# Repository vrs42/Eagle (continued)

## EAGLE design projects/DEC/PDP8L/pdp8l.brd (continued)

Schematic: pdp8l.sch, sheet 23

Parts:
A14: M115; H807
A15, A16: M162; H807
B15: M119; H807
B16, B17: M162; H807
C16: M111; H807

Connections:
!CLR_PARITY_ERROR: A14.M1 (IN3), B15.J2 (OUT)
!MB00: B16.A1 (1B); also elsewhere on the board
!MB01: B16.B1 (2B); also elsewhere on the board
!MB02: B16.C1 (4B); also elsewhere on the board
!MB03: B15.H2 (IN8), B15.N2 (IN8), B16.D1 (8B); also elsewhere on the board
!MB04: B15.F2 (IN7), B15.M2 (IN7), B17.K2 (1B); also elsewhere on the board
!MB05: B17.L2 (2B); also elsewhere on the board
!MB06: B15.D2 (IN5), B15.K2 (IN5), B17.M2 (4B); also elsewhere on the board
!MB07: B15.D1 (IN4), B15.K1 (IN4), B17.N2 (8B); also elsewhere on the board
!MB08: B15.C1 (IN3), B15.J1 (IN3), B16.K2 (1B); also elsewhere on the board
!MB09: B16.L2 (2B); also elsewhere on the board
!MB10: B16.M2 (4B); also elsewhere on the board
!MB11: B16.N2 (8B); also elsewhere on the board
!MEM00: A15.A1 (1B), C16.D2 (OUT)
!MEM01: A15.B1 (2B), C16.E1 (OUT)
!MEM02: A15.C1 (4B), C16.F2 (OUT)
!MEM03: A15.D1 (8B), C16.H1 (OUT)
!MEM04: A16.K2 (1B), C16.J2 (OUT)
!MEM05: A16.L2 (2B), C16.K1 (OUT)
!MEM06: A16.M2 (4B), C16.L2 (OUT)
!MEM07: A16.N2 (8B), C16.M1 (OUT)
!MEM08: A15.K2 (1B), C16.N2 (OUT)
!MEM09: A15.L2 (2B), C16.P1 (OUT)
!MEM10: A15.M2 (4B), C16.R2 (OUT)
!MEM11: A15.N2 (8B), C16.S1 (OUT)
!MEM_P: A16.D1 (8B), C16.B1 (OUT)
!MP_INT: B15.F1 (IN1), C16.T2 (OUT); also elsewhere on the board
!MP_SKIP: B15.P2 (OUT); also elsewhere on the board
A14M2: A14.K1 (IN1), A14.L1 (IN2), A14.M2 (OUT)
A14U1: A14.J2 (IN1), A14.U1 (OUT)
A15K1: A15.K1 (ODD), A16.E1 (1A)
A15L1: A15.L1 (EVEN), A16.A1 (1B)
A15U2: A15.U2 (ODD), A16.H1 (4A)
A15V2: A15.V2 (EVEN), A16.C1 (4B)
A16U2: A16.F1 (2A), A16.U2 (ODD)
A16V2: A16.B1 (2B), A16.V2 (EVEN)
B15U1: B15.U1, B17.D1 (8B)
B16K1: B16.K1 (ODD), B17.E1 (1A)
B16L1: B16.L1 (EVEN), B17.A1 (1B)
B16U2: B16.U2 (ODD), B17.H1 (4A)
B16V2: B16.V2 (EVEN), B17.C1 (4B)
B17U2: B17.F1 (2A), B17.U2 (ODD)
B17V2: B17.B1 (2B), B17.V2 (EVEN)
GND: A14.C2 (GND), A14.T1 (GND), A15.C2 (GND), A15.T1 (GND), A16.C2 (GND), A16.T1 (GND), B15.C2 (GND), B15.T1 (GND), B16.C2 (GND), B16.T1 (GND), B17.C2 (GND), B17.J1 (8A), B17.T1 (GND), C16.C2 (GND), C16.T1 (GND); also elsewhere on the board
IOP1: B15.H1 (IN2); also elsewhere on the board
IOP4: B15.A1 (IN1), B15.B1 (IN2); also elsewhere on the board
MB00: B16.E1 (1A); also elsewhere on the board
MB01: B16.F1 (2A); also elsewhere on the board
MB02: B16.H1 (4A); also elsewhere on the board
MB03: B16.J1 (8A); also elsewhere on the board
MB04: B17.P2 (1A); also elsewhere on the board
MB05: B15.E2 (IN6), B15.L2 (IN6), B17.R2 (2A); also elsewhere on the board
MB06: B17.S2 (4A); also elsewhere on the board
MB07: B17.T2 (8A); also elsewhere on the board
MB08: B16.P2 (1A); also elsewhere on the board
MB09: B16.R2 (2A); also elsewhere on the board
MB10: B16.S2 (4A); also elsewhere on the board
MB11: B16.T2 (8A); also elsewhere on the board
MB_PARITY_ODD: B17.K1 (ODD); also elsewhere on the board
MEM00: A15.E1 (1A), C16.C1 (IN); also elsewhere on the board
MEM01: A15.F1 (2A), C16.D1 (IN); also elsewhere on the board
MEM02: A15.H1 (4A), C16.E2 (IN); also elsewhere on the board
MEM03: A15.J1 (8A), C16.F1 (IN); also elsewhere on the board
MEM04: A16.P2 (1A), C16.H2 (IN); also elsewhere on the board
MEM05: A16.R2 (2A), C16.J1 (IN); also elsewhere on the board
MEM06: A16.S2 (4A), C16.K2 (IN); also elsewhere on the board
MEM07: A16.T2 (8A), C16.L1 (IN); also elsewhere on the board
MEM08: A15.P2 (1A), C16.M2 (IN); also elsewhere on the board
MEM09: A15.R2 (2A), C16.N1 (IN); also elsewhere on the board
MEM10: A15.S2 (4A), C16.P2 (IN); also elsewhere on the board
MEM11: A15.T2 (8A), C16.R1 (IN); also elsewhere on the board
MEM_P: A16.J1 (8A), C16.A1 (IN); also elsewhere on the board
MEM_PARITY_EVEN: A14.P1 (IN1), A14.R1 (IN2), A16.L1 (EVEN)
MP_INT: A14.K2 (IN2), A14.L2 (IN3), A14.N1 (OUT), C16.S2 (IN)
TP3: A14.S1 (IN3); also elsewhere on the board
VCC: A14.A2 (VCC), A15.A2 (VCC), A16.A2 (VCC), B15.A2 (VCC), B16.A2 (VCC), B17.A2 (VCC), C16.A2 (VCC); also elsewhere on the board

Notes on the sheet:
Borrowed Gates from A14 may not match DEC implementation.
Memory Parity

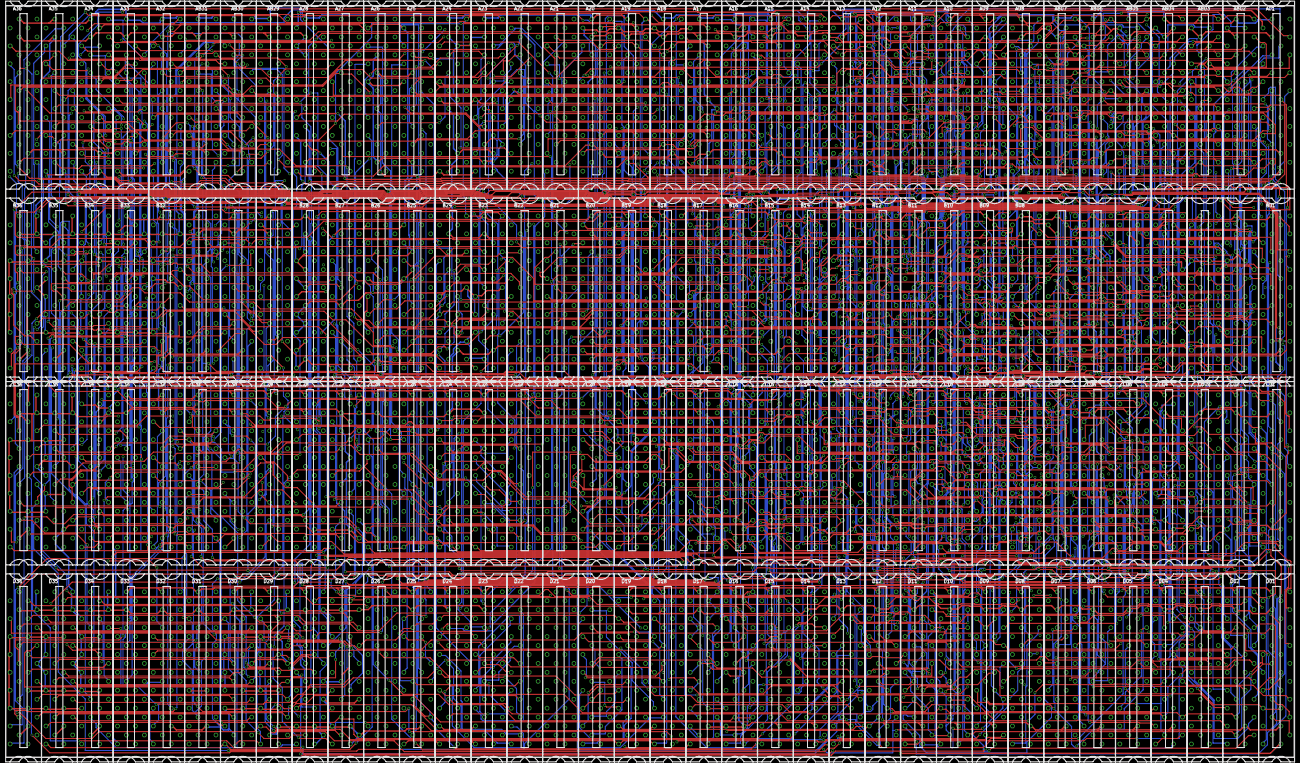
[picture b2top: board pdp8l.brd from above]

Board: 4 copper layers, 457.2 x 266.7 mm, 152 parts (0 on the bottom side), 895 nets.

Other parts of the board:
U$1, U$2, U$3, U$4, U$5, U$6, U$7, U$8, U$9, U$10, U$11, U$12, U$13, U$14, U$15, U$16, U$17, U$18: CBLOCK

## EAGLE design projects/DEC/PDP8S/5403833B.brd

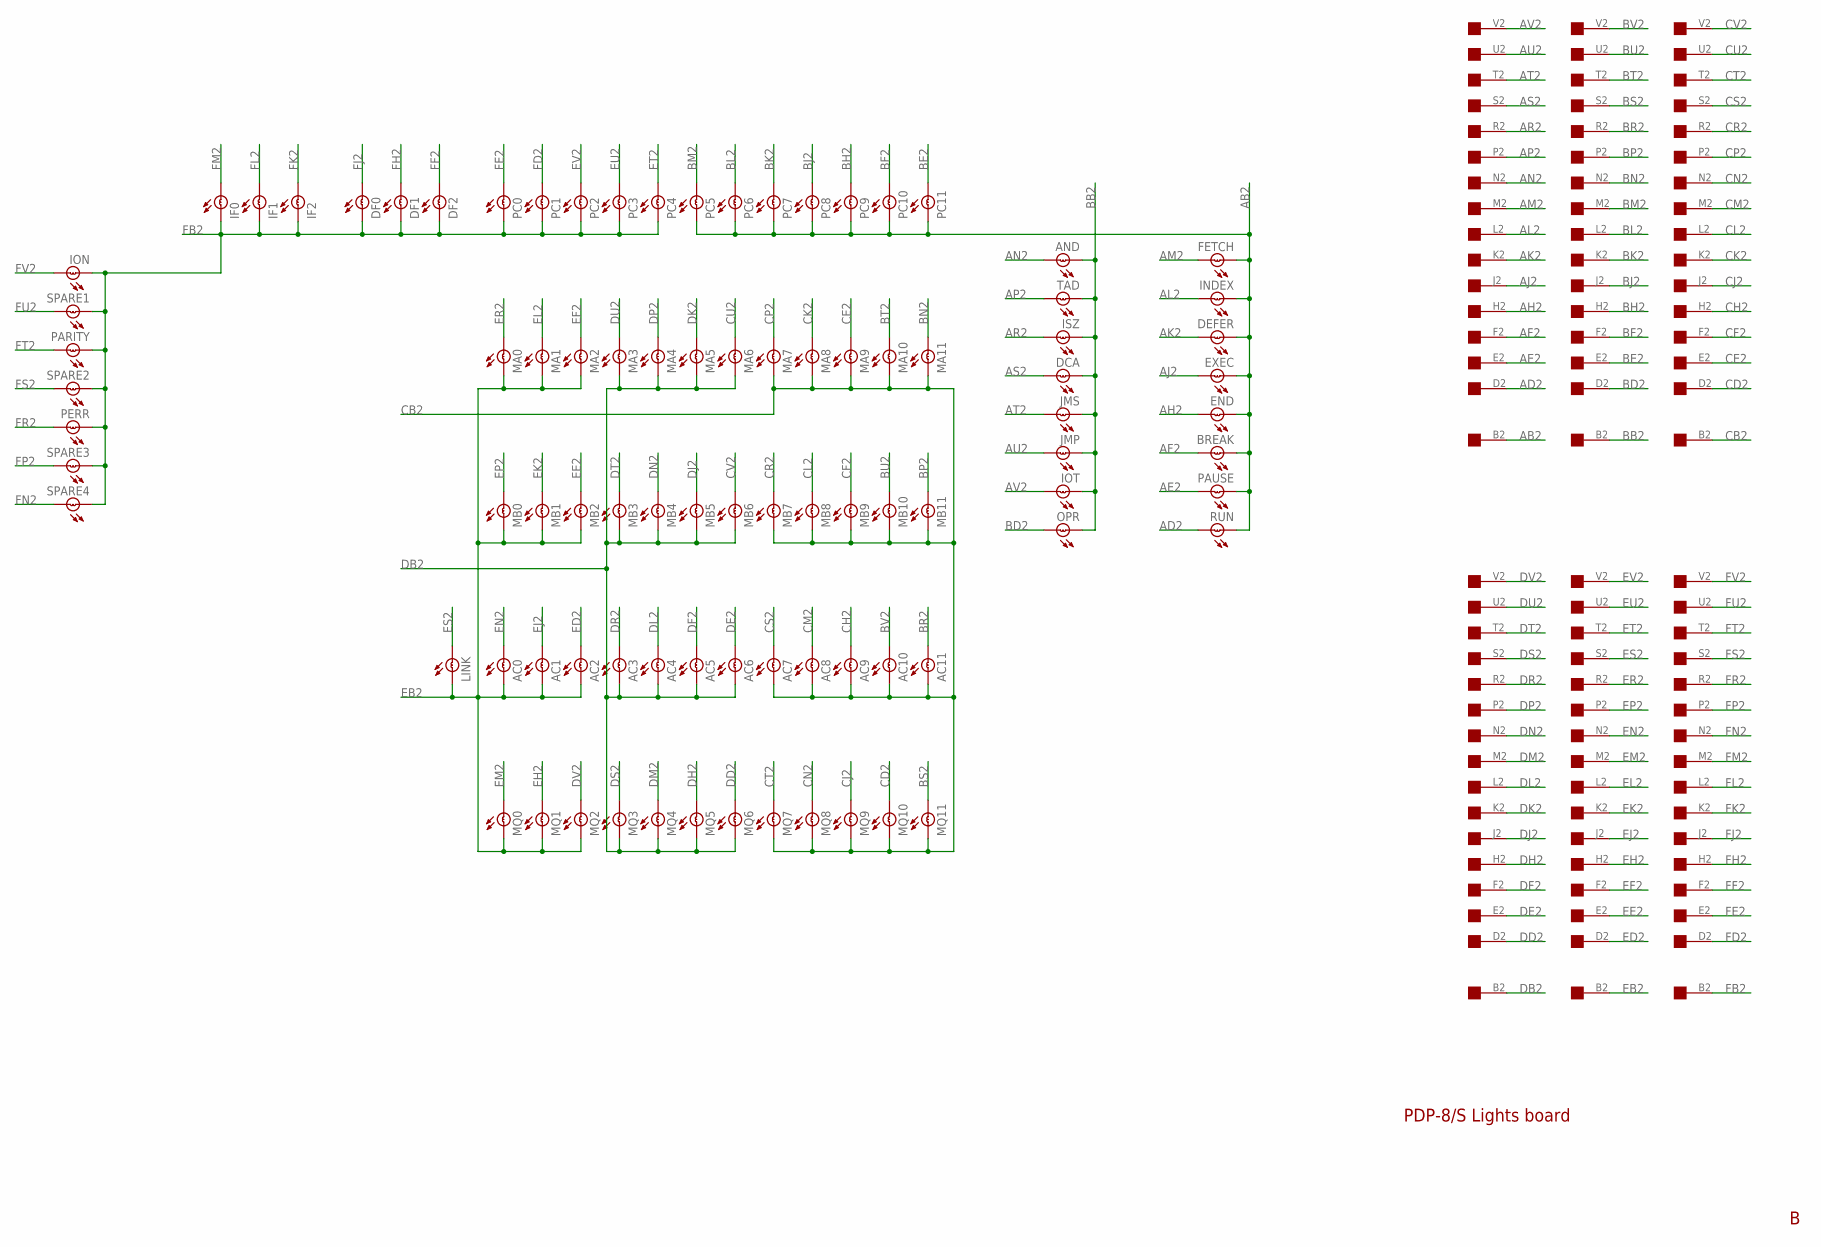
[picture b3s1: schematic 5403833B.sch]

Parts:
A: EDGE-1; EDGE-CON1
AC0, AC1, AC2, AC3, AC4, AC5, AC6, AC7, AC8, AC9, AC10, AC11: BULB
AND: BULB
B: EDGE-1; EDGE-CON1
BREAK: BULB
C: EDGE-1; EDGE-CON1
D: EDGE-1; EDGE-CON1
DCA: BULB
DEFER: BULB
DF0, DF1, DF2: BULB
E: EDGE-1; EDGE-CON1
END: BULB
EXEC: BULB
F: EDGE-1; EDGE-CON1
FETCH: BULB
IF0, IF1, IF2: BULB
INDEX: BULB
ION: BULB
IOT: BULB
ISZ: BULB
JMP: BULB
JMS: BULB
LINK: BULB
MA0, MA1, MA2, MA3, MA4, MA5, MA6, MA7, MA8, MA9, MA10, MA11: BULB
MB0, MB1, MB2, MB3, MB4, MB5, MB6, MB7, MB8, MB9, MB10, MB11: BULB
MQ0, MQ1, MQ2, MQ3, MQ4, MQ5, MQ6, MQ7, MQ8, MQ9, MQ10, MQ11: BULB
OPR: BULB
PARITY: BULB
PAUSE: BULB
PC0, PC1, PC2, PC3, PC4, PC5, PC6, PC7, PC8, PC9, PC10, PC11: BULB
PERR: BULB
RUN: BULB
SPARE1, SPARE2, SPARE3, SPARE4: BULB
TAD: BULB

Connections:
AB2: A.B2, BREAK.B, DEFER.B, END.B, EXEC.B, FETCH.B, INDEX.B, PAUSE.B, PC5.B, PC6.B, PC7.B, PC8.B, PC9.B, PC10.B, PC11.B, RUN.B
AD2: A.D2, RUN.A
AE2: A.E2, PAUSE.A
AF2: A.F2, BREAK.A
AH2: A.H2, END.A
AJ2: A.J2, EXEC.A
AK2: A.K2, DEFER.A
AL2: A.L2, INDEX.A
AM2: A.M2, FETCH.A
AN2: A.N2, AND.A
AP2: A.P2, TAD.A
AR2: A.R2, ISZ.A
AS2: A.S2, DCA.A
AT2: A.T2, JMS.A
AU2: A.U2, JMP.A
AV2: A.V2, IOT.A
BB2: AND.B, B.B2, DCA.B, IOT.B, ISZ.B, JMP.B, JMS.B, OPR.B, TAD.B
BD2: B.D2, OPR.A
BE2: B.E2, PC11.A
BF2: B.F2, PC10.A
BH2: B.H2, PC9.A
BJ2: B.J2, PC8.A
BK2: B.K2, PC7.A
BL2: B.L2, PC6.A
BM2: B.M2, PC5.A
BN2: B.N2, MA11.A
BP2: B.P2, MB11.A
BR2: AC11.A, B.R2
BS2: B.S2, MQ11.A
BT2: B.T2, MA10.A
BU2: B.U2, MB10.A
BV2: AC10.A, B.V2
CB2: AC7.B, AC8.B, AC9.B, AC10.B, AC11.B, C.B2, MA7.B, MA8.B, MA9.B, MA10.B, MA11.B, MB7.B, MB8.B, MB9.B, MB10.B, MB11.B, MQ7.B, MQ8.B, MQ9.B, MQ10.B, MQ11.B
CD2: C.D2, MQ10.A
CE2: C.E2, MA9.A
CF2: C.F2, MB9.A
CH2: AC9.A, C.H2
CJ2: C.J2, MQ9.A
CK2: C.K2, MA8.A
CL2: C.L2, MB8.A
CM2: AC8.A, C.M2
CN2: C.N2, MQ8.A
CP2: C.P2, MA7.A
CR2: C.R2, MB7.A
CS2: AC7.A, C.S2
CT2: C.T2, MQ7.A
CU2: C.U2, MA6.A
CV2: C.V2, MB6.A
DB2: AC3.B, AC4.B, AC5.B, AC6.B, D.B2, MA3.B, MA4.B, MA5.B, MA6.B, MB3.B, MB4.B, MB5.B, MB6.B, MQ3.B, MQ4.B, MQ5.B, MQ6.B
DD2: D.D2, MQ6.A
DE2: AC6.A, D.E2
DF2: AC5.A, D.F2
DH2: D.H2, MQ5.A
DJ2: D.J2, MB5.A
DK2: D.K2, MA5.A
DL2: AC4.A, D.L2
DM2: D.M2, MQ4.A
DN2: D.N2, MB4.A
DP2: D.P2, MA4.A
DR2: AC3.A, D.R2
DS2: D.S2, MQ3.A
DT2: D.T2, MB3.A
DU2: D.U2, MA3.A
DV2: D.V2, MQ2.A
EB2: AC0.B, AC1.B, AC2.B, E.B2, LINK.B, MA0.B, MA1.B, MA2.B, MB0.B, MB1.B, MB2.B, MQ0.B, MQ1.B, MQ2.B
ED2: AC2.A, E.D2
EE2: E.E2, MB2.A
EF2: E.F2, MA2.A
EH2: E.H2, MQ1.A
EJ2: AC1.A, E.J2
EK2: E.K2, MB1.A
EL2: E.L2, MA1.A
EM2: E.M2, MQ0.A
EN2: AC0.A, E.N2
EP2: E.P2, MB0.A
ER2: E.R2, MA0.A
ES2: E.S2, LINK.A
ET2: E.T2, PC4.A
EU2: E.U2, PC3.A
EV2: E.V2, PC2.A
FB2: DF0.B, DF1.B, DF2.B, F.B2, IF0.B, IF1.B, IF2.B, ION.B, PARITY.B, PC0.B, PC1.B, PC2.B, PC3.B, PC4.B, PERR.B, SPARE1.B, SPARE2.B, SPARE3.B, SPARE4.B
FD2: F.D2, PC1.A
FE2: F.E2, PC0.A
FF2: DF2.A, F.F2
FH2: DF1.A, F.H2
FJ2: DF0.A, F.J2
FK2: F.K2, IF2.A
FL2: F.L2, IF1.A
FM2: F.M2, IF0.A
FN2: F.N2, SPARE4.A
FP2: F.P2, SPARE3.A
FR2: F.R2, PERR.A
FS2: F.S2, SPARE2.A
FT2: F.T2, PARITY.A
FU2: F.U2, SPARE1.A
FV2: F.V2, ION.A

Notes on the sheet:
PDP-8/S Lights board

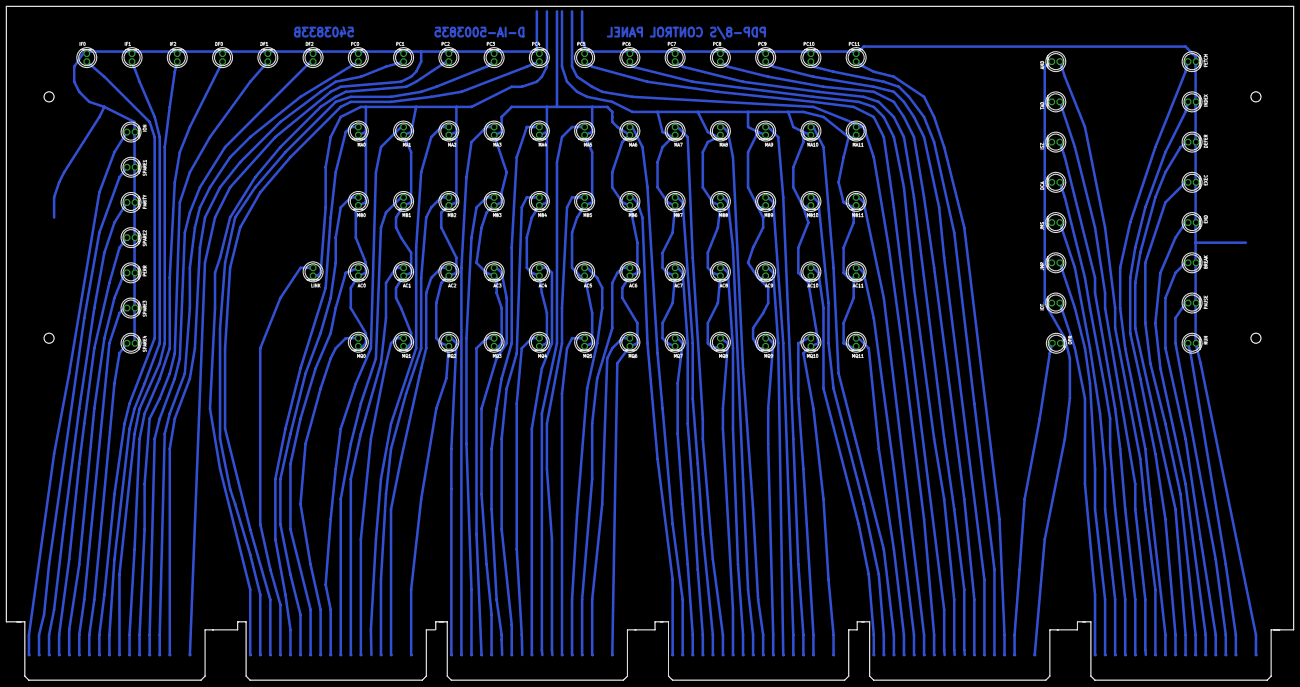
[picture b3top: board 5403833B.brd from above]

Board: 2 copper layers, 406.4 x 212.7 mm, 96 parts (0 on the bottom side), 96 nets.

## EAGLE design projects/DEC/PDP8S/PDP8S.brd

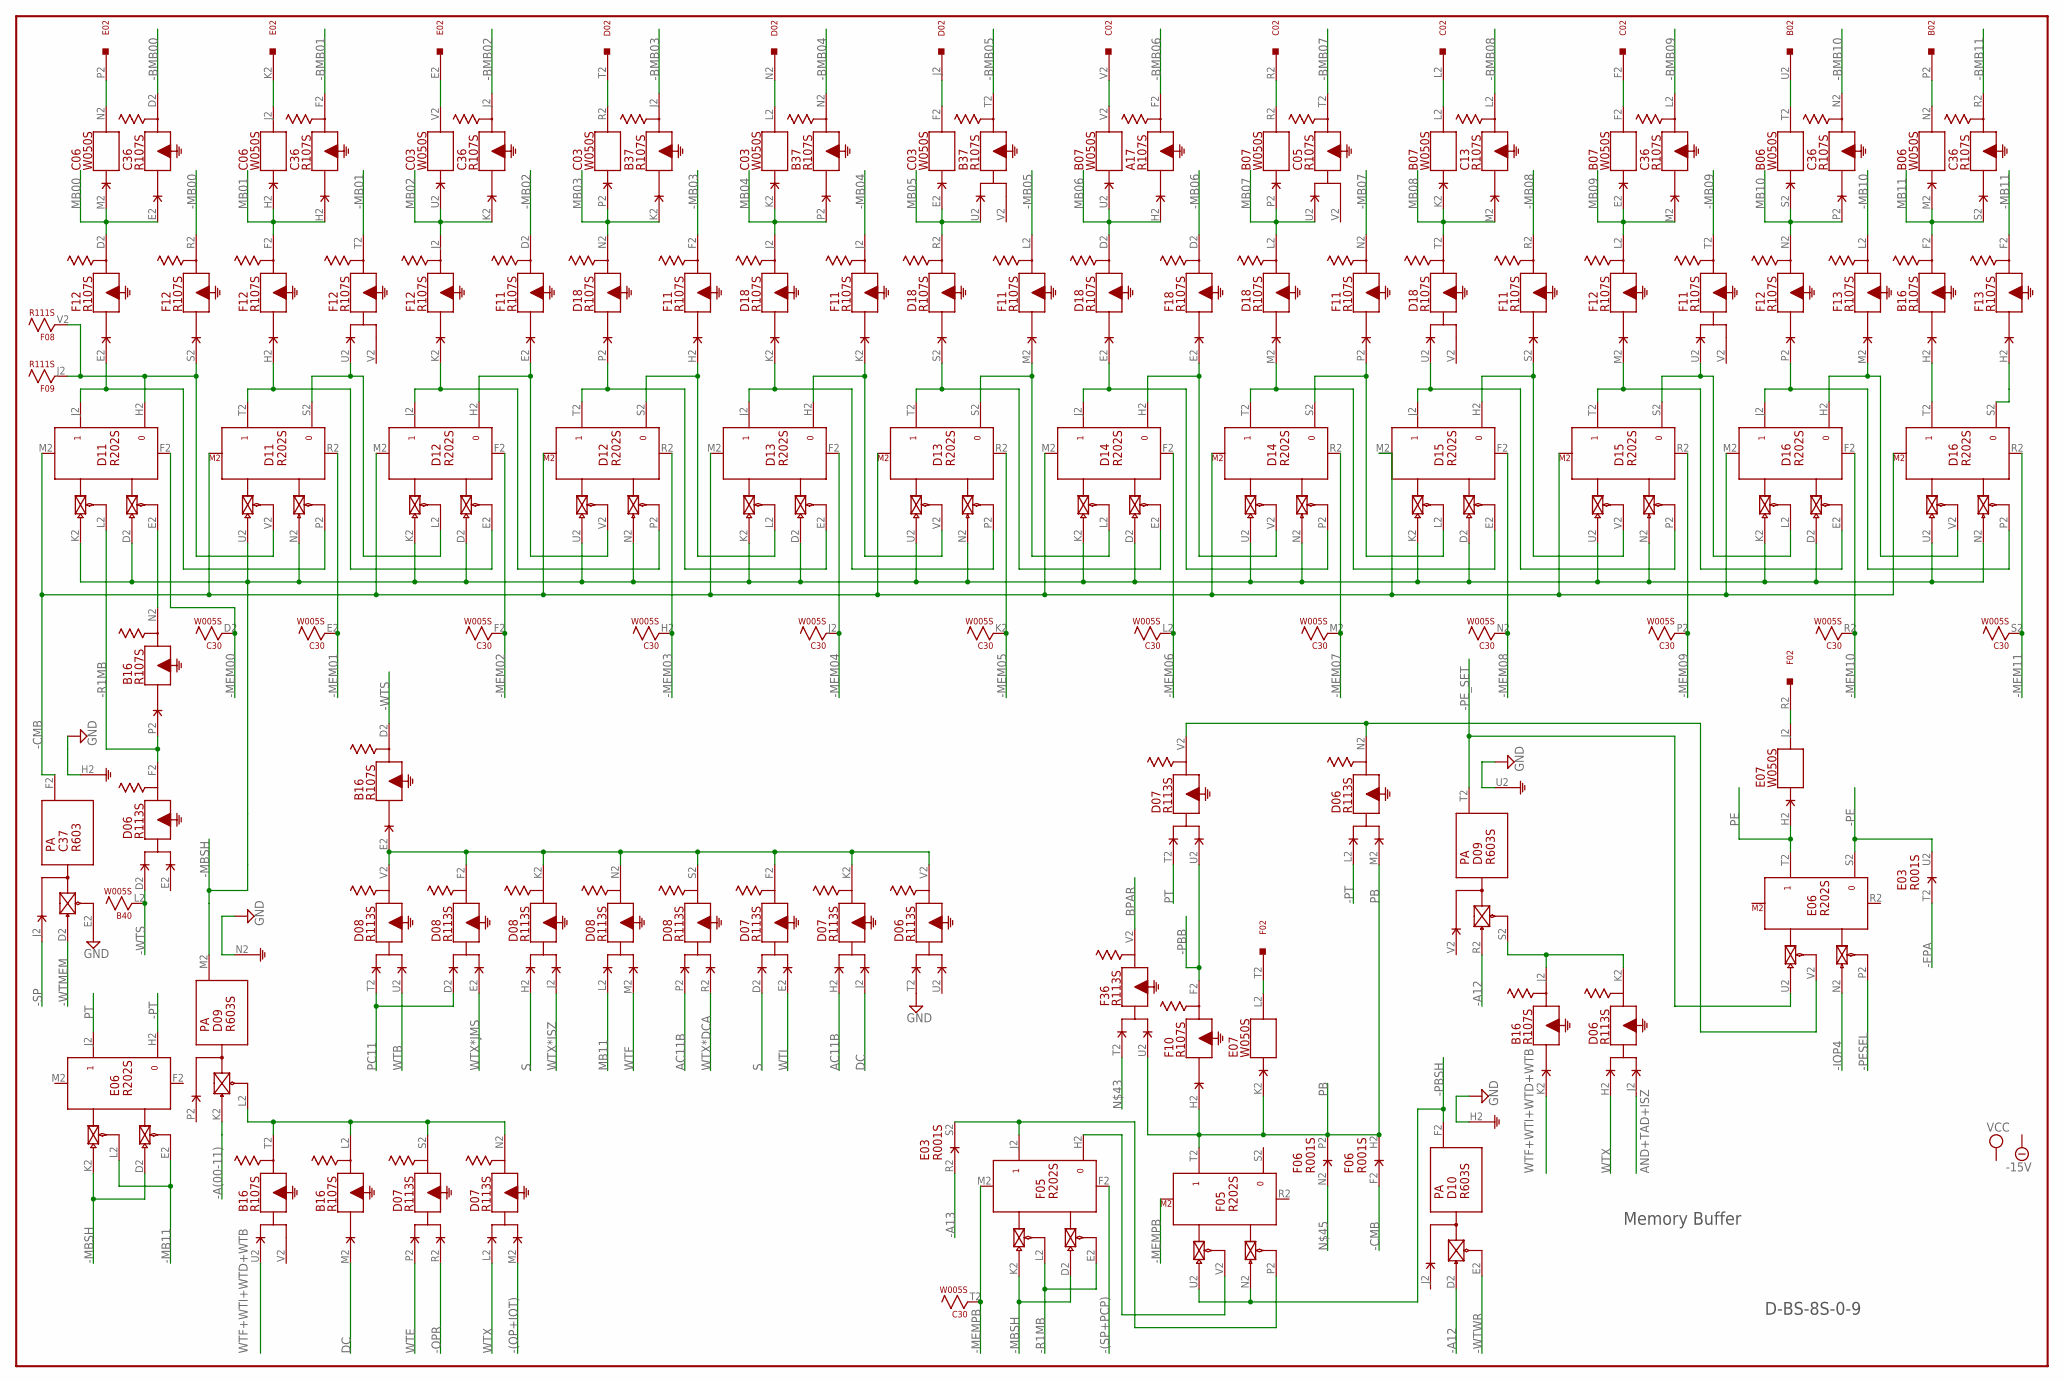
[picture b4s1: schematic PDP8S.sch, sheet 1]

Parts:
A17: R107S; H807S
B02: W023S; H807S
B06, B07: W050S; H807S
B16, B37: R107S; H807S
B40: W005S; H807S
C02: W023S; H807S
C03, C06: W050S; H807S
C05, C13, C36: R107S; H807S
C30: W005S; H807S
C37: R603; H807
D02: W023S; H807S
D06, D07, D08: R113S; H807S
D09, D10: R603S; H807S
D11, D12, D13, D14, D15, D16: R202S; H807S
D18: R107S; H807S
E02: W023S; H807S
E03: R001S; H807S
E06: R202S; H807S
E07: W050S; H807S
F02: W023S; H807S
F05: R202S; H807S
F06: R001S; H807S
F08, F09: R111S; H807S
F10, F11, F12, F13, F18: R107S; H807S
F36: R113S; H807S

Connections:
-15V: A17.B2 (-15V), B06.B2 (-15V), B07.B2 (-15V), B16.B2 (-15V), B37.B2 (-15V), B40.B2 (-15V), C03.B2 (-15V), C05.B2 (-15V), C06.B2 (-15V), C13.B2 (-15V), C30.B2 (-15V), C36.B2 (-15V), C37.B2 (-15V), D06.B2 (-15V), D07.B2 (-15V), D08.B2 (-15V), D09.B2 (-15V), D10.B2 (-15V), D11.B2 (-15V), D12.B2 (-15V), D13.B2 (-15V), D14.B2 (-15V), D15.B2 (-15V), D16.B2 (-15V), D18.B2 (-15V), E03.B2 (-15V), E06.B2 (-15V), E07.B2 (-15V), F05.B2 (-15V), F06.B2 (-15V), F08.B2 (-15V), F09.B2 (-15V), F10.B2 (-15V), F11.B2 (-15V), F12.B2 (-15V), F13.B2 (-15V), F18.B2 (-15V), F36.B2 (-15V)
-(OP+IOT): D07.M2
-(SP+PCP): F05.F2 (RESET)
-A12: D09.R2 (PU0), D10.D2 (PU0)
-A13: E03.R2 (D)
-A(00-11): D09.K2 (PU0)
-BMB00: C36.D2
-BMB01: C36.F2
-BMB02: C36.J2
-BMB03: B37.J2
-BMB04: B37.N2
-BMB05: B37.T2
-BMB06: A17.F2
-BMB07: C05.T2
-BMB08: C13.L2
-BMB09: C36.L2
-BMB10: C36.N2
-BMB11: C36.R2
-CMB: C37.F2 (O), D11.M2 (SET), D12.M2 (SET), D13.M2 (SET), D14.M2 (SET), D15.M2 (SET), D16.M2 (SET), F06.F2 (D)
-EPA: E03.T2 (D)
-IOP4: E06.N2 (PU0)
-MB00: F12.R2
-MB01: F12.T2
-MB02: F11.D2
-MB03: F11.F2
-MB04: F11.J2
-MB05: F11.L2
-MB06: F18.D2
-MB07: F11.N2
-MB08: F11.R2
-MB09: F11.T2
-MB10: F13.L2
-MB11: E06.E2 (EN0), E06.L2 (EN1), F13.F2
-MBSH: D09.M2 (O), D11.D2 (PU0), D11.K2 (PU1), D11.N2 (PU0), D11.U2 (PU1), D12.D2 (PU0), D12.K2 (PU1), D12.N2 (PU0), D12.U2 (PU1), D13.D2 (PU0), D13.K2 (PU1), D13.N2 (PU0), D13.U2 (PU1), D14.D2 (PU0), D14.K2 (PU1), D14.N2 (PU0), D14.U2 (PU1), D15.D2 (PU0), D15.K2 (PU1), D15.N2 (PU0), D15.U2 (PU1), D16.D2 (PU0), D16.K2 (PU1), D16.N2 (PU0), D16.U2 (PU1), E06.D2 (PU0), E06.K2 (PU1), F05.D2 (PU0), F05.K2 (PU1)
-MEM00: C30.D2, D11.F2 (RESET)
-MEM01: C30.E2, D11.R2 (RESET)
-MEM02: C30.F2, D12.F2 (RESET)
-MEM03: C30.H2, D12.R2 (RESET)
-MEM04: C30.J2, D13.F2 (RESET)
-MEM05: C30.K2, D13.R2 (RESET)
-MEM06: C30.L2, D14.F2 (RESET)
-MEM07: C30.M2, D14.R2 (RESET)
-MEM08: C30.N2, D15.F2 (RESET)
-MEM09: C30.P2, D15.R2 (RESET)
-MEM10: C30.R2, D16.F2 (RESET)
-MEM11: C30.S2, D16.R2 (RESET)
-MEMPB: C30.T2, F05.M2 (SET)
-OPR: D07.R2
-PBB: D07.U2, F10.F2
-PBSH: D10.F2 (O), F05.N2 (PU0), F05.U2 (PU1)
-PE: E03.U2 (E), E06.S2 (0)
-PESEL: E06.P2 (EN0)
-PE_SET: D09.T2 (O), E06.U2 (PU1)
-PT: D06.L2, E06.H2 (0)
-R1MB: B16.P2, D06.F2, D11.L2 (EN1), F05.E2 (EN0), F05.L2 (EN1)
-SP: C37.J2
-WTMEM: C37.D2 (PU0)
-WTS: B16.D2, B40.L2, D06.D2
-WTWR: D10.E2 (EN0)
AC11B: D07.H2, D08.P2
AND+TAD+ISZ: D06.J2
BPAR: F36.V2
DC: B16.M2, D07.J2
GND: A17.C2 (GND), B06.C2 (GND), B07.C2 (GND), B16.C2 (GND), B37.C2 (GND), B40.C2 (GND), C03.C2 (GND), C05.C2 (GND), C06.C2 (GND), C13.C2 (GND), C30.C2 (GND), C36.C2 (GND), C37.C2 (GND), C37.E2 (EN0), C37.H2 (G), D06.C2 (GND), D06.T2, D07.C2 (GND), D08.C2 (GND), D09.C2 (GND), D09.N2 (G), D09.U2 (G), D10.C2 (GND), D10.H2 (G), D11.C2 (GND), D12.C2 (GND), D13.C2 (GND), D14.C2 (GND), D15.C2 (GND), D16.C2 (GND), D18.C2 (GND), E03.C2 (GND), E06.C2 (GND), E07.C2 (GND), F05.C2 (GND), F06.C2 (GND), F08.C2 (GND), F09.C2 (GND), F10.C2 (GND), F11.C2 (GND), F12.C2 (GND), F13.C2 (GND), F18.C2 (GND), F36.C2 (GND)
MB00: C06.M2, C36.E2, F12.D2
MB01: C06.H2, C36.H2, F12.F2
MB02: C03.U2, C36.K2, F12.J2
MB03: B37.K2, C03.P2, D18.N2
MB04: B37.P2, C03.K2, D18.J2
MB05: B37.U2, C03.E2, D18.R2
MB06: A17.H2, B07.U2, D18.D2
MB07: B07.P2, C05.U2, D18.L2
MB08: B07.K2, C13.M2, D18.T2
MB09: B07.E2, C36.M2, F12.L2
MB10: B06.S2, C36.P2, F12.N2
MB11: B06.M2, B16.F2, C36.S2, D08.L2
unnamed: D11.J2 (1), D11.P2 (EN0), F12.E2
unnamed: C06.N2, E02.P2
unnamed: D11.H2 (0), D11.V2 (EN1), F08.V2, F09.J2, F12.S2
unnamed: D11.T2 (1), D12.E2 (EN0), F12.H2
unnamed: B16.E2, D06.V2, D07.F2, D07.K2, D08.F2, D08.K2, D08.N2, D08.S2, D08.V2
unnamed: D12.J2 (1), D12.P2 (EN0), F12.K2
unnamed: D12.T2 (1), D13.E2 (EN0), D18.P2
unnamed: D13.J2 (1), D13.P2 (EN0), D18.K2
unnamed: D13.T2 (1), D14.E2 (EN0), D18.S2
unnamed: D14.J2 (1), D14.P2 (EN0), D18.E2
unnamed: D14.T2 (1), D15.E2 (EN0), D18.M2
unnamed: D15.J2 (1), D15.P2 (EN0), D18.U2
unnamed: D15.H2 (0), D15.V2 (EN1), F11.S2
unnamed: D14.S2 (0), D15.L2 (EN1), F11.P2
unnamed: D14.H2 (0), D14.V2 (EN1), F18.E2
unnamed: D13.S2 (0), D14.L2 (EN1), F11.M2
unnamed: D15.T2 (1), D16.E2 (EN0), F12.M2
unnamed: D15.S2 (0), D16.L2 (EN1), F11.U2
unnamed: D16.J2 (1), D16.P2 (EN0), F12.P2
unnamed: D13.H2 (0), D13.V2 (EN1), F11.K2
unnamed: D12.S2 (0), D13.L2 (EN1), F11.H2
unnamed: D12.H2 (0), D12.V2 (EN1), F11.E2
unnamed: D11.S2 (0), D12.L2 (EN1), F12.U2
unnamed: D16.H2 (0), D16.V2 (EN1), F13.M2
unnamed: B16.H2, D16.T2 (1)
unnamed: D16.S2 (0), F13.H2
unnamed: C06.J2, E02.K2
unnamed: C03.V2, E02.E2
unnamed: C03.R2, D02.T2
unnamed: C03.L2, D02.N2
unnamed: C03.F2, D02.J2
unnamed: B07.V2, C02.V2
unnamed: B07.R2, C02.R2
unnamed: B07.L2, C02.L2
unnamed: B07.F2, C02.F2
unnamed: B02.U2, B06.T2
unnamed: B02.P2, B06.N2
unnamed: B16.L2, B16.T2, D07.N2, D07.S2, D09.L2 (EN0)
unnamed: B16.N2, D11.E2 (EN0)
unnamed: B16.J2, D06.K2, D09.S2 (EN0)
unnamed: E07.J2, F02.R2
unnamed: D06.N2, D07.V2, E06.V2 (EN1)
unnamed: E07.L2, F02.T2
unnamed: F05.H2 (0), F05.V2 (EN1)
unnamed: E03.S2 (E), F05.J2 (1), F05.P2 (EN0)
PB: D06.M2, E07.K2, F05.T2 (1), F06.H2 (E), F06.P2 (E), F10.H2, F36.U2
PC11: D08.D2, D08.T2
PE: E06.T2 (1), E07.H2
PT: D07.T2, E06.J2 (1)
S: D07.D2, D08.H2
VCC: A17.A2 (VCC), B06.A2 (VCC), B07.A2 (VCC), B16.A2 (VCC), B37.A2 (VCC), B40.A2 (VCC), C03.A2 (VCC), C05.A2 (VCC), C06.A2 (VCC), C13.A2 (VCC), C30.A2 (VCC), C36.A2 (VCC), C37.A2 (VCC), D06.A2 (VCC), D07.A2 (VCC), D08.A2 (VCC), D09.A2 (VCC), D10.A2 (VCC), D11.A2 (VCC), D12.A2 (VCC), D13.A2 (VCC), D14.A2 (VCC), D15.A2 (VCC), D16.A2 (VCC), D18.A2 (VCC), E03.A2 (VCC), E06.A2 (VCC), E07.A2 (VCC), F05.A2 (VCC), F06.A2 (VCC), F08.A2 (VCC), F09.A2 (VCC), F10.A2 (VCC), F11.A2 (VCC), F12.A2 (VCC), F13.A2 (VCC), F18.A2 (VCC), F36.A2 (VCC)
WTB: D08.U2
WTE: D07.P2
WTF: D08.M2
WTF+WTI+WTD+WTB: B16.K2, B16.U2
WTI: D07.E2
WTX: D06.H2, D07.L2
WTX*DCA: D08.R2
WTX*ISZ: D08.J2
WTX*JMS: D08.E2

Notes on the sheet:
D-BS-8S-0-9
Memory Buffer

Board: 2 copper layers, 73 parts (0 on the bottom side), 93 nets, no tracks yet.

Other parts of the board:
U$1, U$2, U$3, U$4, U$5, U$6, U$7, U$8, U$9, U$10, U$11, U$12, U$13, U$14, U$15, U$16, U$17, U$18, U$19, U$20, U$21, U$22, U$23, U$24, U$25, U$26, U$27, U$28, U$29, U$30: CBLOCK
